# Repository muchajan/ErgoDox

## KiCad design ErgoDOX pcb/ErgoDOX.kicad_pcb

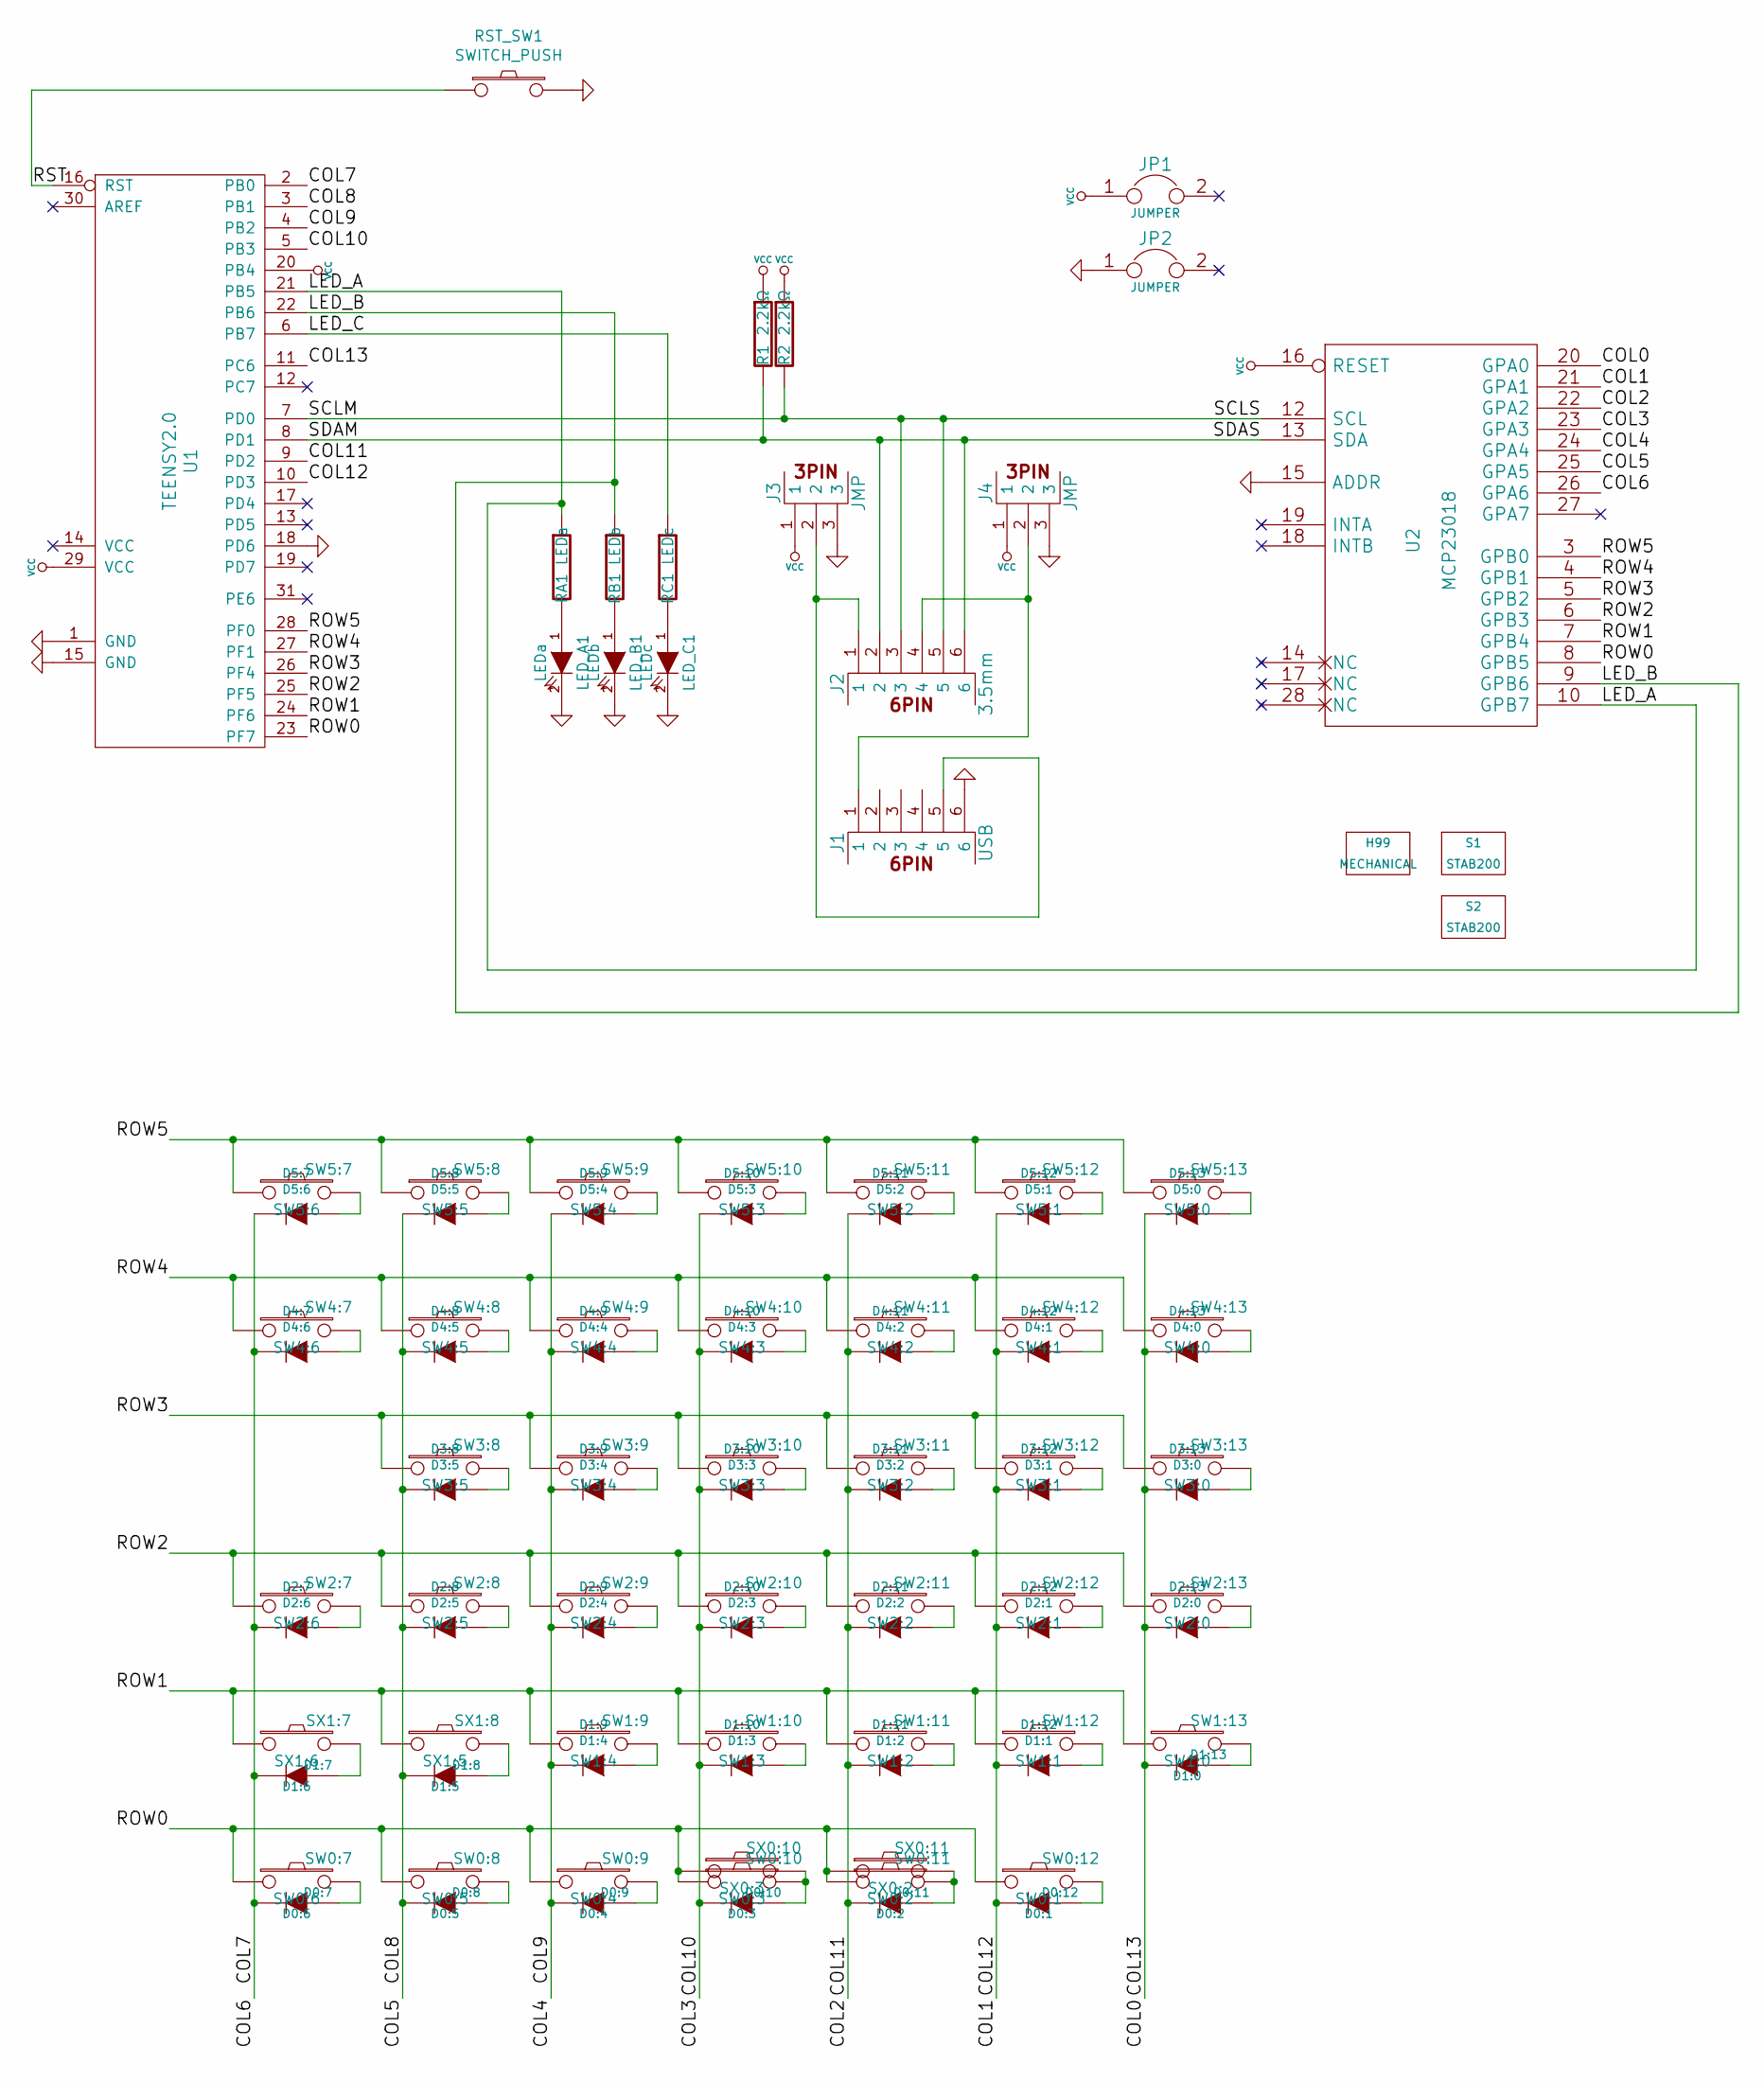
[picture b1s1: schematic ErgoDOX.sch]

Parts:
D0:7: D0:6; D_DO-35_SOD27_P7.62mm_Horizontal
D0:8: D0:5; D_DO-35_SOD27_P7.62mm_Horizontal
D0:9: D0:4; D_DO-35_SOD27_P7.62mm_Horizontal
D0:10: D0:3; D_DO-35_SOD27_P7.62mm_Horizontal
D0:11: D0:2; D_DO-35_SOD27_P7.62mm_Horizontal
D0:12: D0:1; D_DO-35_SOD27_P7.62mm_Horizontal
D1:7: D1:6; D_DO-35_SOD27_P7.62mm_Horizontal
D1:8: D1:5; D_DO-35_SOD27_P7.62mm_Horizontal
D1:9: D1:4; D_DO-35_SOD27_P7.62mm_Horizontal
D1:10: D1:3; D_DO-35_SOD27_P7.62mm_Horizontal
D1:11: D1:2; D_DO-35_SOD27_P7.62mm_Horizontal
D1:12: D1:1; D_DO-35_SOD27_P7.62mm_Horizontal
D1:13: D1:0; D_DO-35_SOD27_P7.62mm_Horizontal
D2:7: D2:6; D_DO-35_SOD27_P7.62mm_Horizontal
D2:8: D2:5; D_DO-35_SOD27_P7.62mm_Horizontal
D2:9: D2:4; D_DO-35_SOD27_P7.62mm_Horizontal
D2:10: D2:3; D_DO-35_SOD27_P7.62mm_Horizontal
D2:11: D2:2; D_DO-35_SOD27_P7.62mm_Horizontal
D2:12: D2:1; D_DO-35_SOD27_P7.62mm_Horizontal
D2:13: D2:0; D_DO-35_SOD27_P7.62mm_Horizontal
D3:8: D3:5; D_DO-35_SOD27_P7.62mm_Horizontal
D3:9: D3:4; D_DO-35_SOD27_P7.62mm_Horizontal
D3:10: D3:3; D_DO-35_SOD27_P7.62mm_Horizontal
D3:11: D3:2; D_DO-35_SOD27_P7.62mm_Horizontal
D3:12: D3:1; D_DO-35_SOD27_P7.62mm_Horizontal
D3:13: D3:0; D_DO-35_SOD27_P7.62mm_Horizontal
D4:7: D4:6; D_DO-35_SOD27_P7.62mm_Horizontal
D4:8: D4:5; D_DO-35_SOD27_P7.62mm_Horizontal
D4:9: D4:4; D_DO-35_SOD27_P7.62mm_Horizontal
D4:10: D4:3; D_DO-35_SOD27_P7.62mm_Horizontal
D4:11: D4:2; D_DO-35_SOD27_P7.62mm_Horizontal
D4:12: D4:1; D_DO-35_SOD27_P7.62mm_Horizontal
D4:13: D4:0; D_DO-35_SOD27_P7.62mm_Horizontal
D5:7: D5:6; D_DO-35_SOD27_P7.62mm_Horizontal
D5:8: D5:5; D_DO-35_SOD27_P7.62mm_Horizontal
D5:9: D5:4; D_DO-35_SOD27_P7.62mm_Horizontal
D5:10: D5:3; D_DO-35_SOD27_P7.62mm_Horizontal
D5:11: D5:2; D_DO-35_SOD27_P7.62mm_Horizontal
D5:12: D5:1; D_DO-35_SOD27_P7.62mm_Horizontal
D5:13: D5:0; D_DO-35_SOD27_P7.62mm_Horizontal
H99: MECHANICAL; ErgoDOXmech
J1: USB; USBMINImod
J2: 3.5mm; 4pin35mmAudio
J3, J4: JMP; 100PITCH1X3
JP1, JP2: JUMPER; GAP
LED_A1: LEDa; MX_LED
LED_B1: LEDb; MX_LED
LED_C1: LEDc; MX_LED
R1, R2: 2.2kΩ; RESISTOR
RA1: LEDa; RESISTOR
RB1: LEDb; RESISTOR
RC1: LEDc; RESISTOR
RST_SW1: SWITCH_PUSH; SW_SPST_B3U-1000P
S1, S2: STAB200; STAB_PCB940
SW0:7: SW0:6; SW_PG1350_reversible
SW0:8: SW0:5; SW_PG1350_reversible
SW0:9: SW0:4; SW_PG1350_reversible
SW0:10: SW0:3; SW_PG1350_reversible
SW0:11: SW0:2; SW_PG1350_reversible
SW0:12: SW0:1; SW_PG1350_reversible
SW1:9: SW1:4; SW_PG1350_reversible
SW1:10: SW1:3; SW_PG1350_reversible
SW1:11: SW1:2; SW_PG1350_reversible
SW1:12: SW1:1; SW_PG1350_reversible
SW1:13: SW1:0; SW_PG1350_reversible
SW2:7: SW2:6; SW_PG1350_reversible
SW2:8: SW2:5; SW_PG1350_reversible
SW2:9: SW2:4; SW_PG1350_reversible
SW2:10: SW2:3; SW_PG1350_reversible
SW2:11: SW2:2; SW_PG1350_reversible
SW2:12: SW2:1; SW_PG1350_reversible
SW2:13: SW2:0; SW_PG1350_reversible
SW3:8: SW3:5; SW_PG1350_reversible
SW3:9: SW3:4; SW_PG1350_reversible
SW3:10: SW3:3; SW_PG1350_reversible
SW3:11: SW3:2; SW_PG1350_reversible
SW3:12: SW3:1; SW_PG1350_reversible
SW3:13: SW3:0; SW_PG1350_reversible
SW4:7: SW4:6; SW_PG1350_reversible
SW4:8: SW4:5; SW_PG1350_reversible
SW4:9: SW4:4; SW_PG1350_reversible
SW4:10: SW4:3; SW_PG1350_reversible
SW4:11: SW4:2; SW_PG1350_reversible
SW4:12: SW4:1; SW_PG1350_reversible
SW4:13: SW4:0; SW_PG1350_reversible
SW5:7: SW5:6; SW_PG1350_reversible
SW5:8: SW5:5; SW_PG1350_reversible
SW5:9: SW5:4; SW_PG1350_reversible
SW5:10: SW5:3; SW_PG1350_reversible
SW5:11: SW5:2; SW_PG1350_reversible
SW5:12: SW5:1; SW_PG1350_reversible
SW5:13: SW5:0; SW_PG1350_reversible
SX0:10: SX0:3; SW_PG1350_reversible
SX0:11: SX0:2; SW_PG1350_reversible
SX1:7: SX1:6; SW_PG1350_reversible
SX1:8: SX1:5; SW_PG1350_reversible
U1: TEENSY2.0; TEENSY_2.0
U2: MCP23018; DIP28_300

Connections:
/COL0: D1:13.2 (K), D2:13.2 (K), D3:13.2 (K), D4:13.2 (K), D5:13.2 (K), U1.11 (PC6), U2.20 (GPA0)
/COL1: D0:12.2 (K), D1:12.2 (K), D2:12.2 (K), D3:12.2 (K), D4:12.2 (K), D5:12.2 (K), U1.10 (PD3), U2.21 (GPA1)
/COL4: D0:9.2 (K), D1:9.2 (K), D2:9.2 (K), D3:9.2 (K), D4:9.2 (K), D5:9.2 (K), U1.4 (PB2), U2.24 (GPA4)
/COL5: D0:8.2 (K), D1:8.2 (K), D2:8.2 (K), D3:8.2 (K), D4:8.2 (K), D5:8.2 (K), U1.3 (PB1), U2.25 (GPA5)
/COL6: D0:7.2 (K), D1:7.2 (K), D2:7.2 (K), D4:7.2 (K), D5:7.2 (K), U1.2 (PB0), U2.26 (GPA6)
/COL10: D0:10.2 (K), D1:10.2 (K), D2:10.2 (K), D3:10.2 (K), D4:10.2 (K), D5:10.2 (K), U1.5 (PB3), U2.23 (GPA3)
/COL11: D0:11.2 (K), D1:11.2 (K), D2:11.2 (K), D3:11.2 (K), D4:11.2 (K), D5:11.2 (K), U1.9 (PD2), U2.22 (GPA2)
/LED_A: RA1.1, U1.21 (PB5), U2.10 (GPB7)
/LED_B: RB1.1, U1.22 (PB6), U2.9 (GPB6)
/LED_C: RC1.1, U1.6 (PB7)
/ROW0: SW0:7.1, SW0:8.1, SW0:9.1, SW0:10.1, SW0:11.1, SW0:12.1, SX0:10.1, SX0:11.1, U1.23 (PF7), U2.8 (GPB5)
/ROW1: SW1:9.1, SW1:10.1, SW1:11.1, SW1:12.1, SW1:13.1, SX1:7.1, SX1:8.1, U1.24 (PF6), U2.7 (GPB4)
/ROW2: SW2:7.1, SW2:8.1, SW2:9.1, SW2:10.1, SW2:11.1, SW2:12.1, SW2:13.1, U1.25 (PF5), U2.6 (GPB3)
/ROW3: SW3:8.1, SW3:9.1, SW3:10.1, SW3:11.1, SW3:12.1, SW3:13.1, U1.26 (PF4), U2.5 (GPB2)
/ROW4: SW4:7.1, SW4:8.1, SW4:9.1, SW4:10.1, SW4:11.1, SW4:12.1, SW4:13.1, U1.27 (PF1), U2.4 (GPB1)
/ROW5: SW5:7.1, SW5:8.1, SW5:9.1, SW5:10.1, SW5:11.1, SW5:12.1, SW5:13.1, U1.28 (PF0), U2.3 (GPB0)
/RST: RST_SW1.1, U1.16 (RST)
/SCLM: J2.3, J2.5, R2.2, U1.7 (PD0), U2.12 (SCL)
/SDAM: J2.2, J2.6, R1.2, U1.8 (PD1), U2.13 (SDA)
GND: J1.6, J3.3, J4.3, JP2.1, LED_A1.2 (K), LED_B1.2 (K), LED_C1.2 (K), RST_SW1.2, U1.1 (GND), U1.15 (GND), U1.18 (PD6), U2.1 (GND), U2.15 (ADDR)
unnamed: D0:7.1 (A), SW0:7.2
unnamed: D0:8.1 (A), SW0:8.2
unnamed: D0:9.1 (A), SW0:9.2
unnamed: D0:10.1 (A), SW0:10.2, SX0:10.2
unnamed: D0:11.1 (A), SW0:11.2, SX0:11.2
unnamed: D0:12.1 (A), SW0:12.2
unnamed: D1:7.1 (A), SX1:7.2
unnamed: D1:8.1 (A), SX1:8.2
unnamed: D1:9.1 (A), SW1:9.2
unnamed: D1:10.1 (A), SW1:10.2
unnamed: D1:11.1 (A), SW1:11.2
unnamed: D1:12.1 (A), SW1:12.2
unnamed: D1:13.1 (A), SW1:13.2
unnamed: D2:7.1 (A), SW2:7.2
unnamed: D2:8.1 (A), SW2:8.2
unnamed: D2:9.1 (A), SW2:9.2
unnamed: D2:10.1 (A), SW2:10.2
unnamed: D2:11.1 (A), SW2:11.2
unnamed: D2:12.1 (A), SW2:12.2
unnamed: D2:13.1 (A), SW2:13.2
unnamed: D3:8.1 (A), SW3:8.2
unnamed: D3:9.1 (A), SW3:9.2
unnamed: D3:10.1 (A), SW3:10.2
unnamed: D3:11.1 (A), SW3:11.2
unnamed: D3:12.1 (A), SW3:12.2
unnamed: D3:13.1 (A), SW3:13.2
unnamed: D4:7.1 (A), SW4:7.2
unnamed: D4:8.1 (A), SW4:8.2
unnamed: D4:9.1 (A), SW4:9.2
unnamed: D4:10.1 (A), SW4:10.2
unnamed: D4:11.1 (A), SW4:11.2
unnamed: D4:12.1 (A), SW4:12.2
unnamed: D4:13.1 (A), SW4:13.2
unnamed: D5:7.1 (A), SW5:7.2
unnamed: D5:8.1 (A), SW5:8.2
unnamed: D5:9.1 (A), SW5:9.2
unnamed: D5:10.1 (A), SW5:10.2
unnamed: D5:11.1 (A), SW5:11.2
unnamed: D5:12.1 (A), SW5:12.2
unnamed: D5:13.1 (A), SW5:13.2
unnamed: J1.1, J2.4, J4.2
unnamed: J1.5, J2.1, J3.2
unnamed: LED_A1.1 (A), RA1.2
unnamed: LED_B1.1 (A), RB1.2
unnamed: LED_C1.1 (A), RC1.2
VCC: J3.1, J4.1, JP1.1, R1.1, R2.1, U1.20 (PB4), U1.29 (VCC), U2.11 (VCC), U2.16 (RESET)

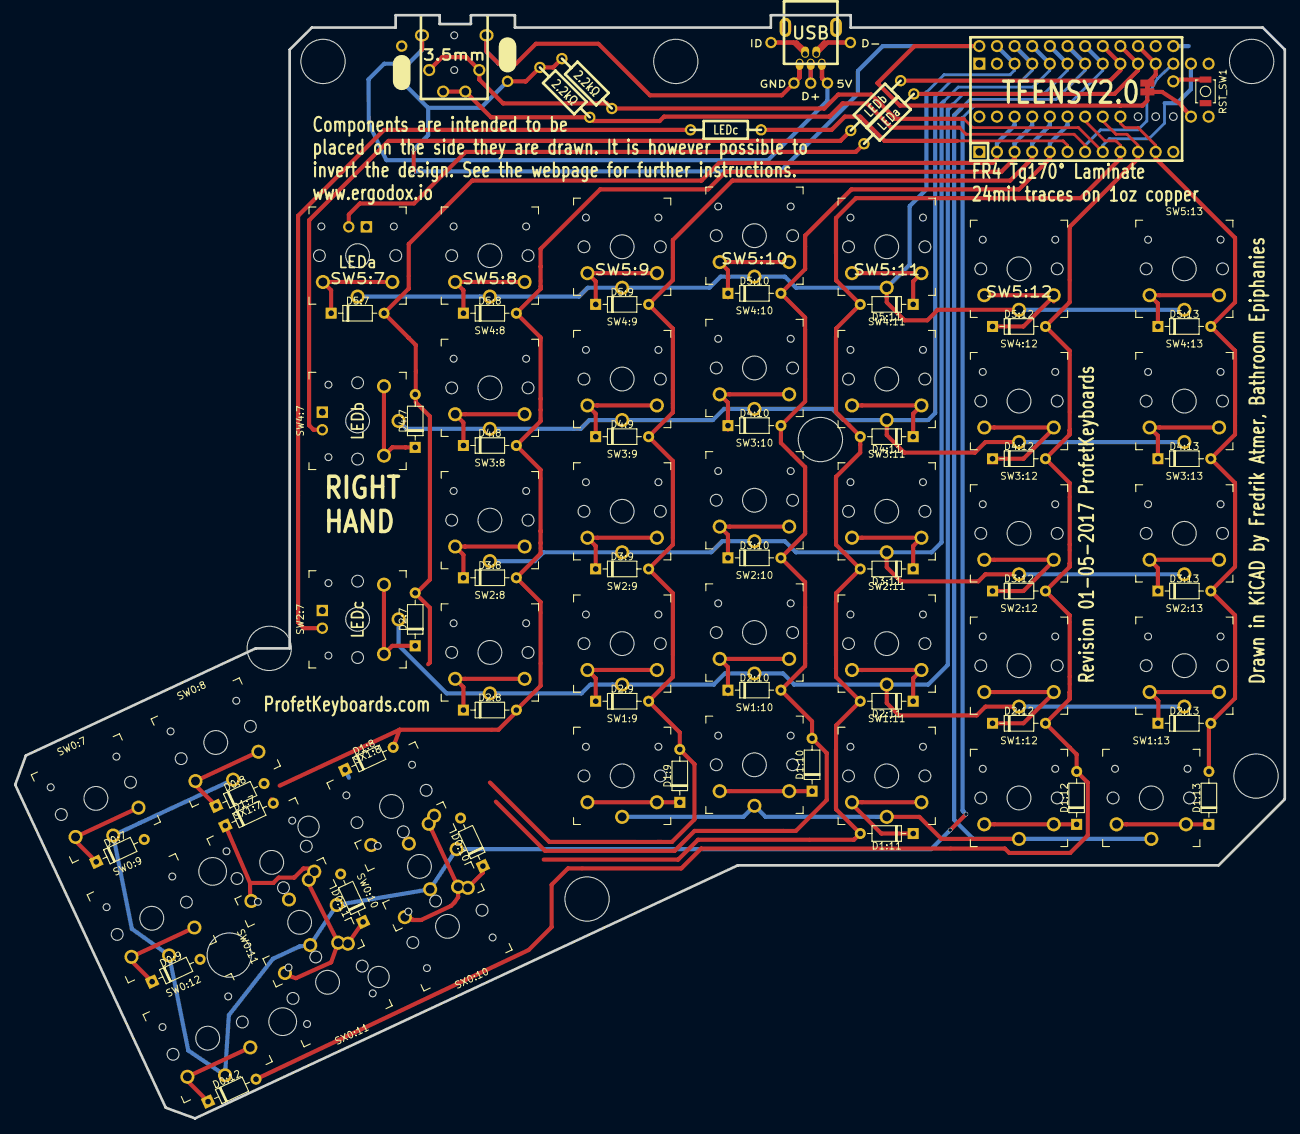
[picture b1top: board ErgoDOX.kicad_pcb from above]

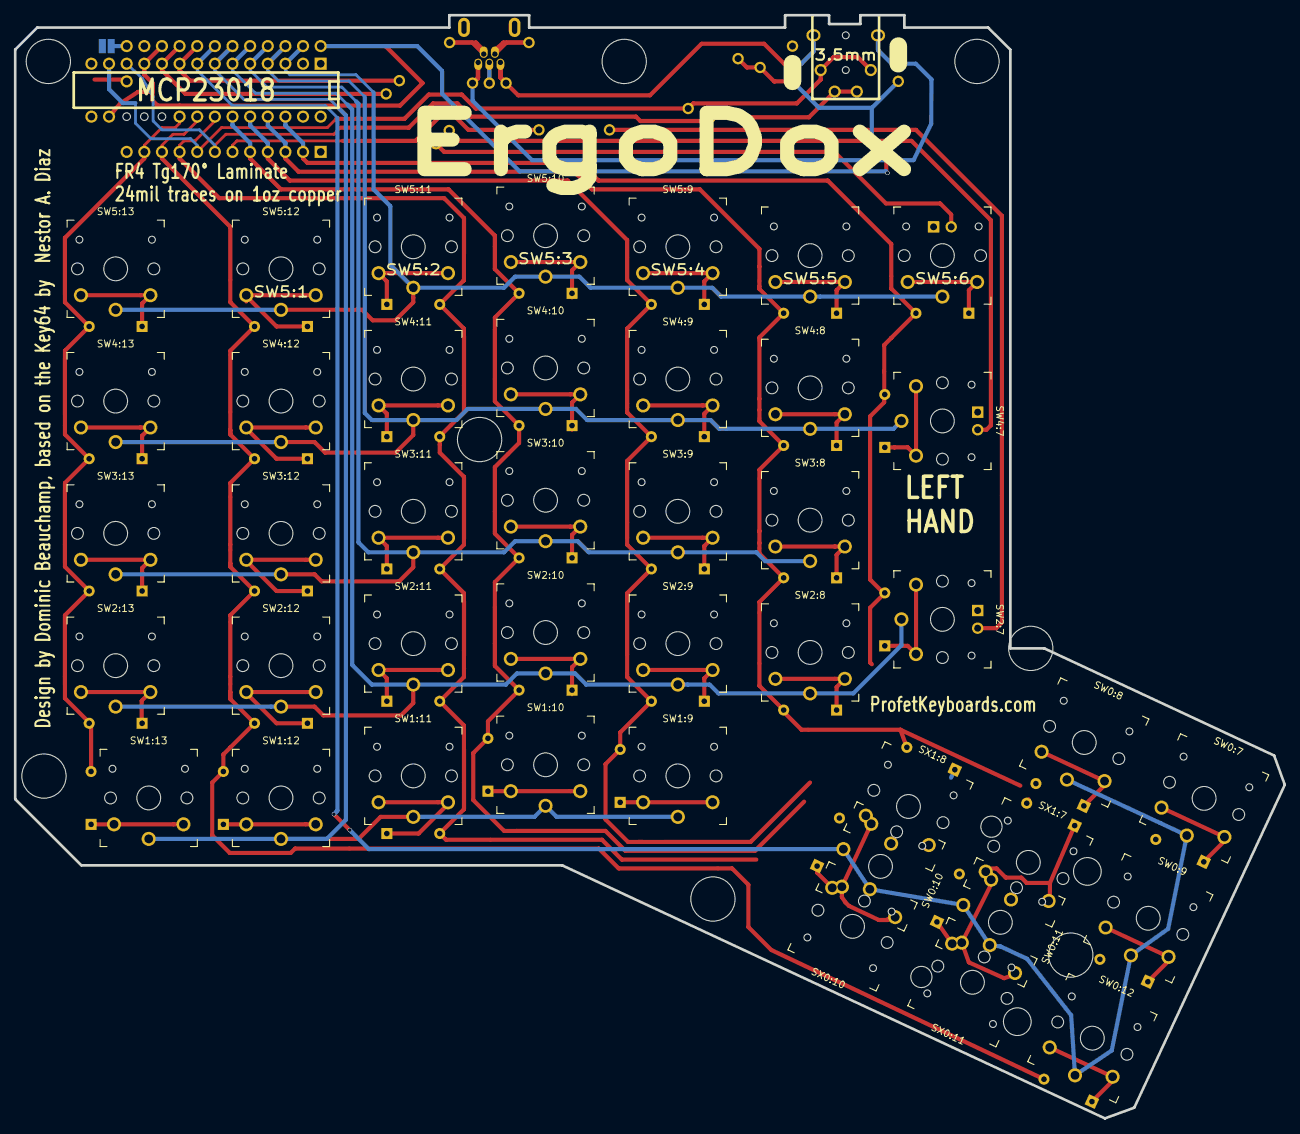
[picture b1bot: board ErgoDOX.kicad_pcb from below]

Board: 2 copper layers, 182.8 x 158.9 mm, 101 parts (3 on the bottom side), 66 nets.

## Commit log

2020-02-15 Added submodule for Kailh Choc switches
2020-02-18 //WIP
    Switches replaced
2020-02-22 WIP placement.py script, some routing
2020-02-26 placement, routing
2020-06-17 //WIP
    routing
